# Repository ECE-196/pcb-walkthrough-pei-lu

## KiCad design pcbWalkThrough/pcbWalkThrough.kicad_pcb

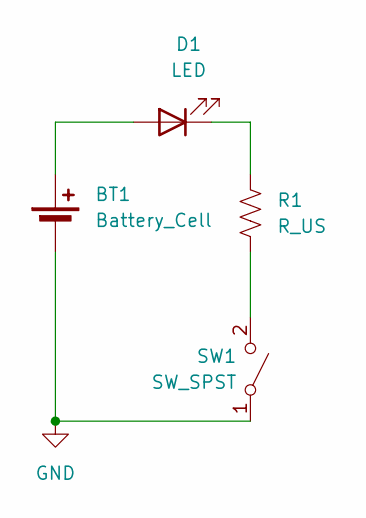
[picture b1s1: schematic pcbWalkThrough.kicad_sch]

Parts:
BT1: Battery_Cell; BatteryHolder_Keystone_103_1x20mm
D1: LED; LED_2512_6332Metric
R1: R_US; R_2512_6332Metric
SW1: SW_SPST; SW_PUSH_6mm

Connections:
GND: BT1.2 (-), SW1.1 (A)
unnamed: BT1.1 (+), D1.2 (A)
unnamed: D1.1 (K), R1.2
unnamed: R1.1, SW1.2 (B)

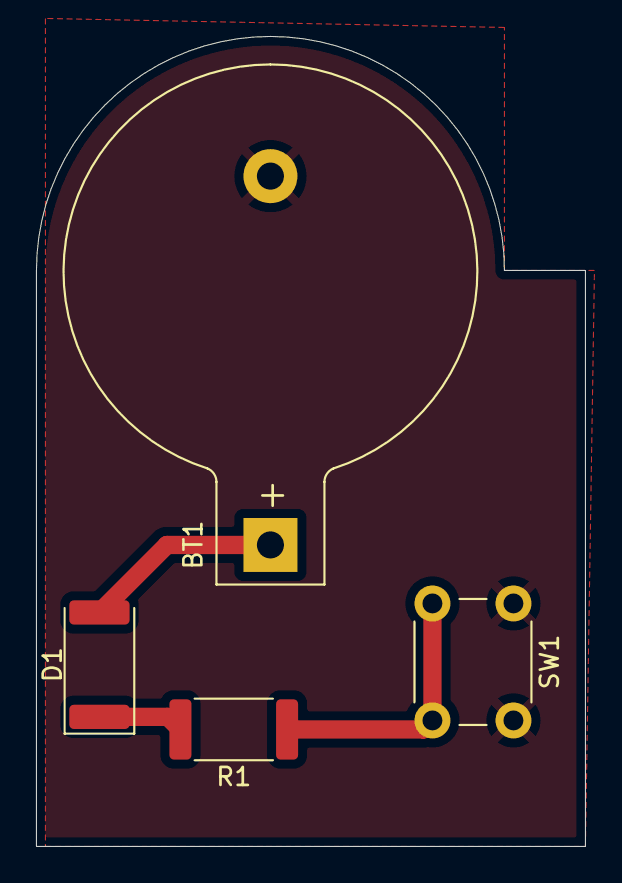
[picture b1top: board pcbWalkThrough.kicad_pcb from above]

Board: 2 copper layers, 30.5 x 45.0 mm, 4 parts (0 on the bottom side), 4 nets.

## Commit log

2024-10-08 finishedhw
2024-10-10 update pcb
